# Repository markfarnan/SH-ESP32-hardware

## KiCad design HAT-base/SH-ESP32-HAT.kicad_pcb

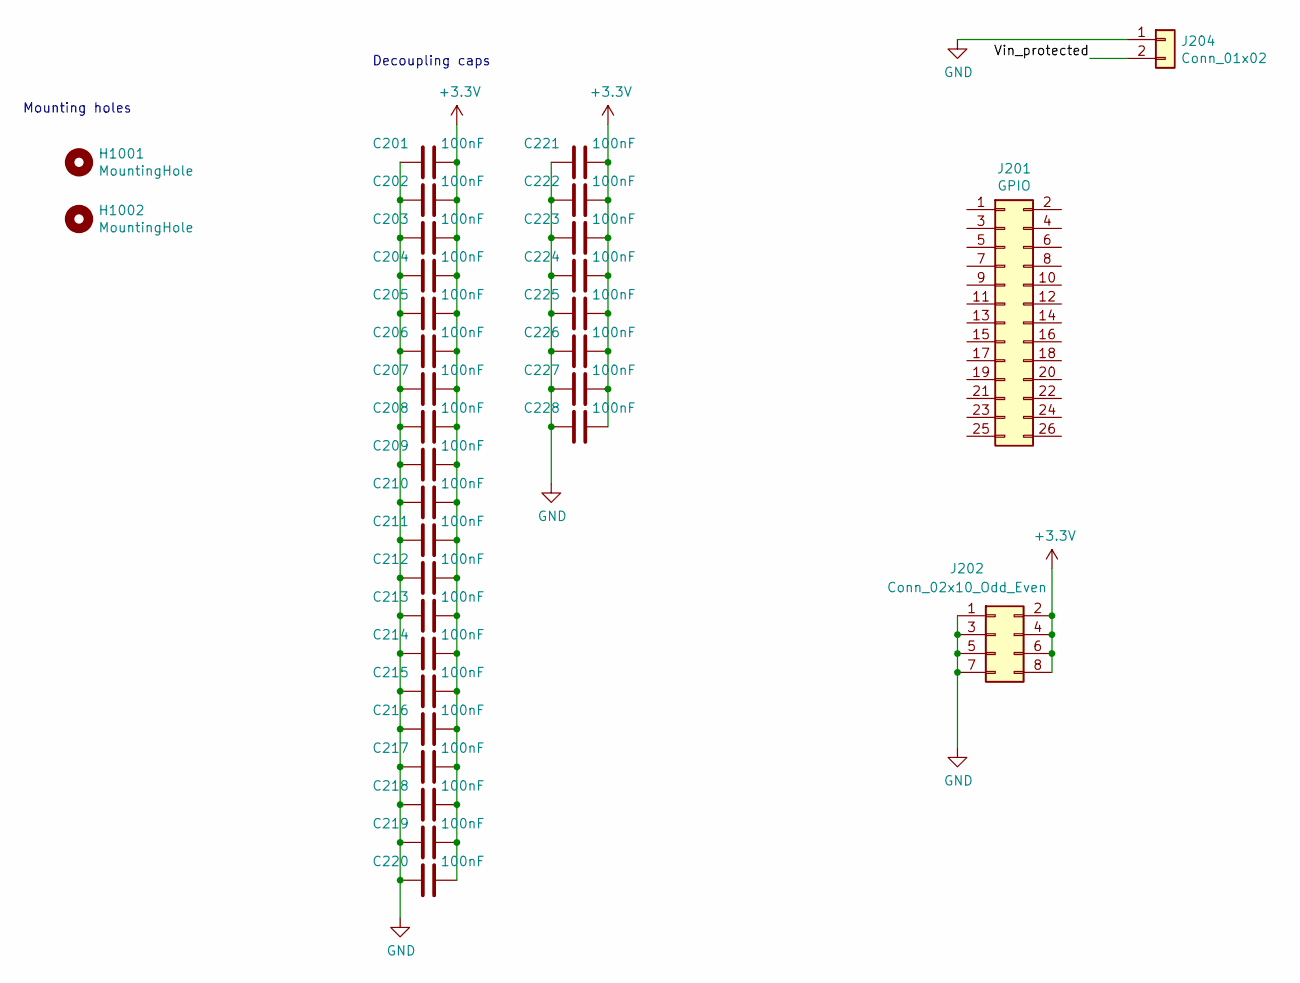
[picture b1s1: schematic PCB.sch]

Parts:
C201, C202, C203, C204, C205, C206, C207, C208, C209, C210, C211, C212, C213, C214, C215, C216, C217, C218, C219, C220, C221, C222, C223, C224, C225, C226, C227, C228: 100nF; C_0402_1005Metric; LCSC C1525
H1001, H1002: MountingHole; MountingHole_3.2mm_M3_Unplated
J201: GPIO; PinHeader_2x13_P2.54mm_Vertical; LCSC C358701
J202: Conn_02x10_Odd_Even; PinHeader_2x04_P2.54mm_Vertical; LCSC C358699
J204: Conn_01x02; PinHeader_1x02_P2.54mm_Vertical; LCSC C376075

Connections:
+3V3: C201.2, C202.2, C203.2, C204.2, C205.2, C206.2, C207.2, C208.2, C209.2, C210.2, C211.2, C212.2, C213.2, C214.2, C215.2, C216.2, C217.2, C218.2, C219.2, C220.2, C221.2, C222.2, C223.2, C224.2, C225.2, C226.2, C227.2, C228.2, J202.2, J202.4, J202.6, J202.8
/PCB/Vin_protected: J204.2
GND: C201.1, C202.1, C203.1, C204.1, C205.1, C206.1, C207.1, C208.1, C209.1, C210.1, C211.1, C212.1, C213.1, C214.1, C215.1, C216.1, C217.1, C218.1, C219.1, C220.1, C221.1, C222.1, C223.1, C224.1, C225.1, C226.1, C227.1, C228.1, J202.1, J202.3, J202.5, J202.7, J204.1

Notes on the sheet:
Mounting holes
Decoupling caps

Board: 4 copper layers, 33 parts (0 on the bottom side), 2 nets, no tracks yet.

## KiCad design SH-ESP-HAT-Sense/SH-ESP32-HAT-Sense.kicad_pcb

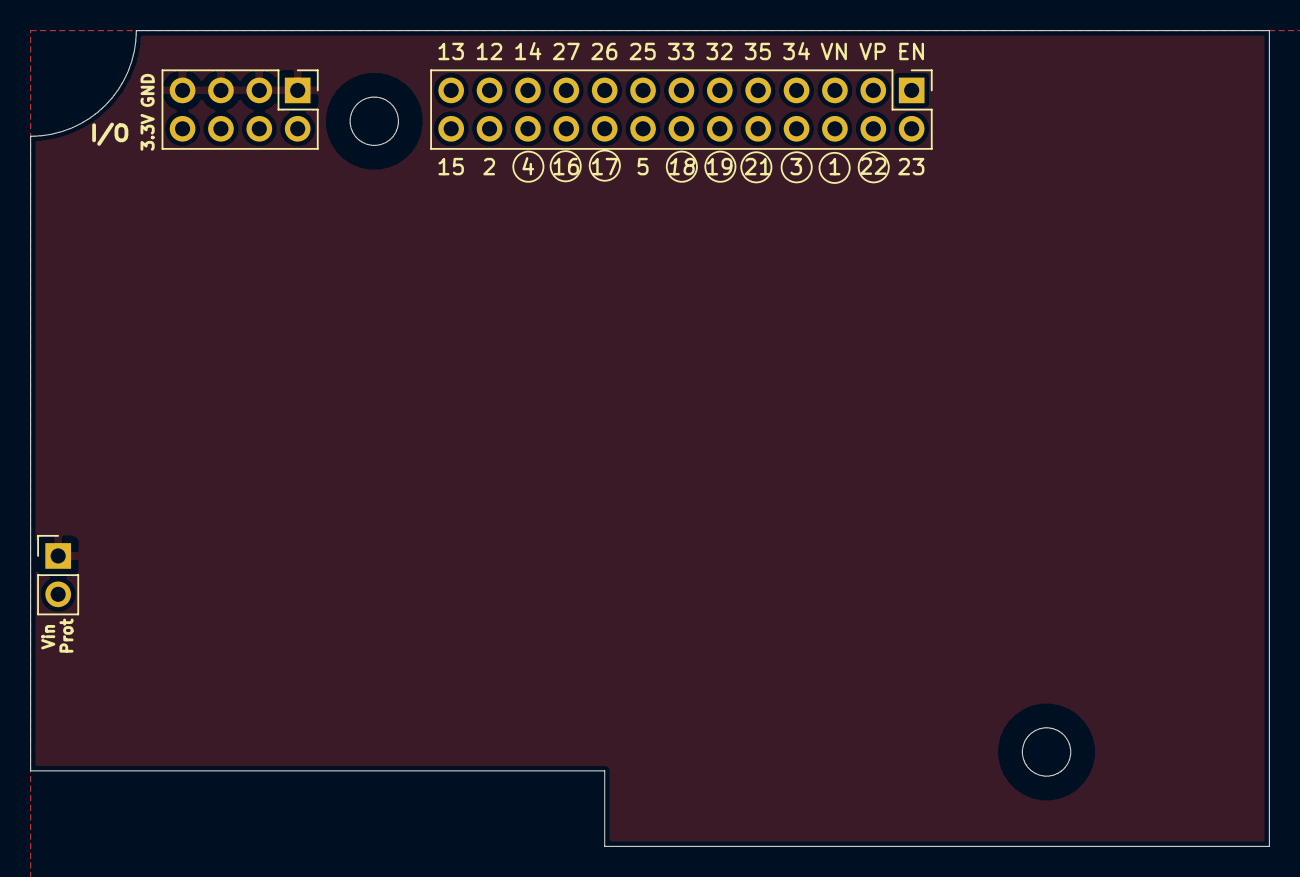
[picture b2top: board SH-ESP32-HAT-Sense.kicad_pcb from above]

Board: 4 copper layers, 82.0 x 54.0 mm, 5 parts (0 on the bottom side), 2 nets.

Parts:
H1001, H1002: MountingHole; MountingHole_3.2mm_M3_Unplated
J201: GPIO; PinHeader_2x13_P2.54mm_Vertical
J202: Conn_02x10_Odd_Even; PinHeader_2x04_P2.54mm_Vertical
J204: Conn_01x02; PinHeader_1x02_P2.54mm_Vertical

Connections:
+3V3: J202.2, J202.4, J202.6, J202.8
GND: J202.1, J202.3, J202.5, J202.7, J204.1

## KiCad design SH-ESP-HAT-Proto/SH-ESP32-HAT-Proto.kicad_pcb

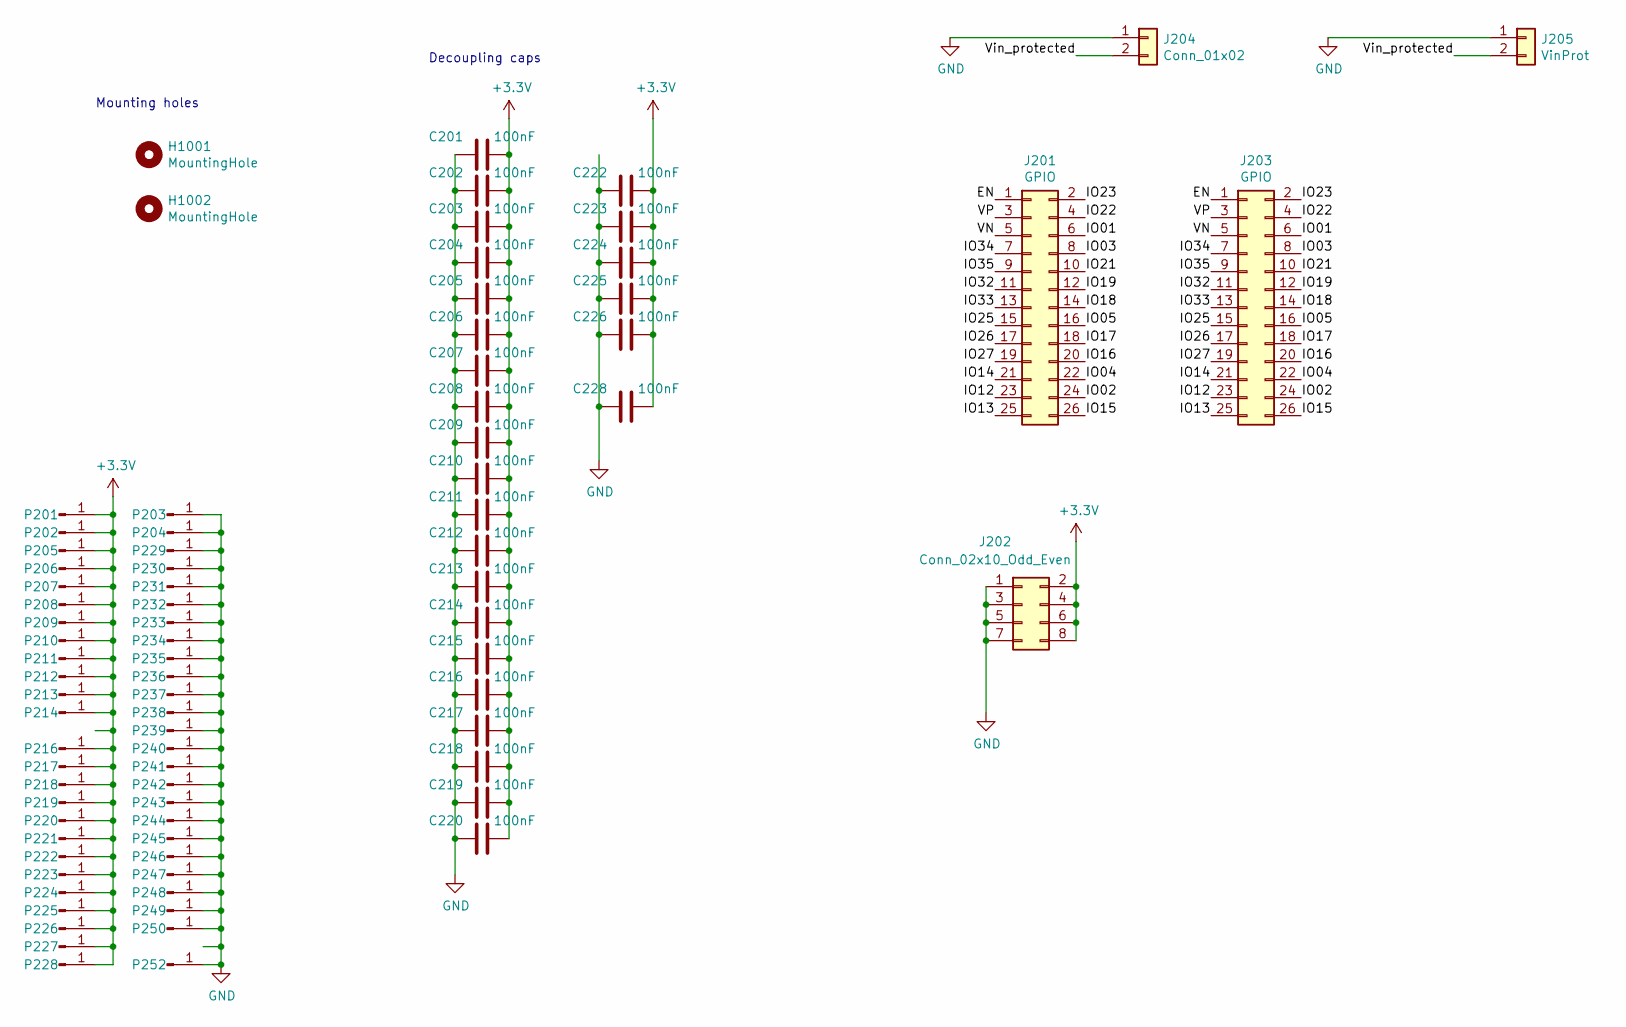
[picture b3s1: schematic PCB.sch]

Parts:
C201, C202, C203, C204, C205, C206, C207, C208, C209, C210, C211, C212, C213, C214, C215, C216, C217, C218, C219, C220, C222, C223, C224, C225, C226, C228: 100nF; C_0402_1005Metric; LCSC C1525
H1001, H1002: MountingHole; MountingHole_3.2mm_M3_Unplated
J201, J203: GPIO; PinHeader_2x13_P2.54mm_Vertical; LCSC C358701
J202: Conn_02x10_Odd_Even; PinHeader_2x04_P2.54mm_Vertical; LCSC C358699
J204: Conn_01x02; PinHeader_1x02_P2.54mm_Vertical; LCSC C376075
J205: VinProt; PinHeader_1x02_P2.54mm_Vertical; LCSC C376075
P201, P202, P203, P204, P205, P206, P207, P208, P209, P210, P211, P212, P213, P214, P216, P217, P218, P219, P220, P221, P222, P223, P224, P225, P226, P227, P228, P229, P230, P231, P232, P233, P234, P235, P236, P237, P238, P239, P240, P241, P242, P243, P244, P245, P246, P247, P248, P249, P250, P252: Conn_01x01_Male; ProtoPad-Drill1mm

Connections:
+3V3: C201.2, C202.2, C203.2, C204.2, C205.2, C206.2, C207.2, C208.2, C209.2, C210.2, C211.2, C212.2, C213.2, C214.2, C215.2, C216.2, C217.2, C218.2, C219.2, C220.2, C222.2, C223.2, C224.2, C225.2, C226.2, C228.2, J202.2, J202.4, J202.6, J202.8, P201.1, P202.1, P205.1, P206.1, P207.1, P208.1, P209.1, P210.1, P211.1, P212.1, P213.1, P214.1, P216.1, P217.1, P218.1, P219.1, P220.1, P221.1, P222.1, P223.1, P224.1, P225.1, P226.1, P227.1, P228.1
/PCB/EN: J201.1, J203.1
/PCB/IO01: J201.6, J203.6
/PCB/IO02: J201.24, J203.24
/PCB/IO03: J201.8, J203.8
/PCB/IO04: J201.22, J203.22
/PCB/IO05: J201.16, J203.16
/PCB/IO12: J201.23, J203.23
/PCB/IO13: J201.25, J203.25
/PCB/IO14: J201.21, J203.21
/PCB/IO15: J201.26, J203.26
/PCB/IO16: J201.20, J203.20
/PCB/IO17: J201.18, J203.18
/PCB/IO18: J201.14, J203.14
/PCB/IO19: J201.12, J203.12
/PCB/IO21: J201.10, J203.10
/PCB/IO22: J201.4, J203.4
/PCB/IO23: J201.2, J203.2
/PCB/IO25: J201.15, J203.15
/PCB/IO26: J201.17, J203.17
/PCB/IO27: J201.19, J203.19
/PCB/IO32: J201.11, J203.11
/PCB/IO33: J201.13, J203.13
/PCB/IO34: J201.7, J203.7
/PCB/IO35: J201.9, J203.9
/PCB/VN: J201.5, J203.5
/PCB/VP: J201.3, J203.3
/PCB/Vin_protected: J204.2, J205.2
GND: C201.1, C202.1, C203.1, C204.1, C205.1, C206.1, C207.1, C208.1, C209.1, C210.1, C211.1, C212.1, C213.1, C214.1, C215.1, C216.1, C217.1, C218.1, C219.1, C220.1, C222.1, C223.1, C224.1, C225.1, C226.1, C228.1, J202.1, J202.3, J202.5, J202.7, J204.1, J205.1, P203.1, P204.1, P229.1, P230.1, P231.1, P232.1, P233.1, P234.1, P235.1, P236.1, P237.1, P238.1, P239.1, P240.1, P241.1, P242.1, P243.1, P244.1, P245.1, P246.1, P247.1, P248.1, P249.1, P250.1, P252.1

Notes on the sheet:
Mounting holes
Decoupling caps

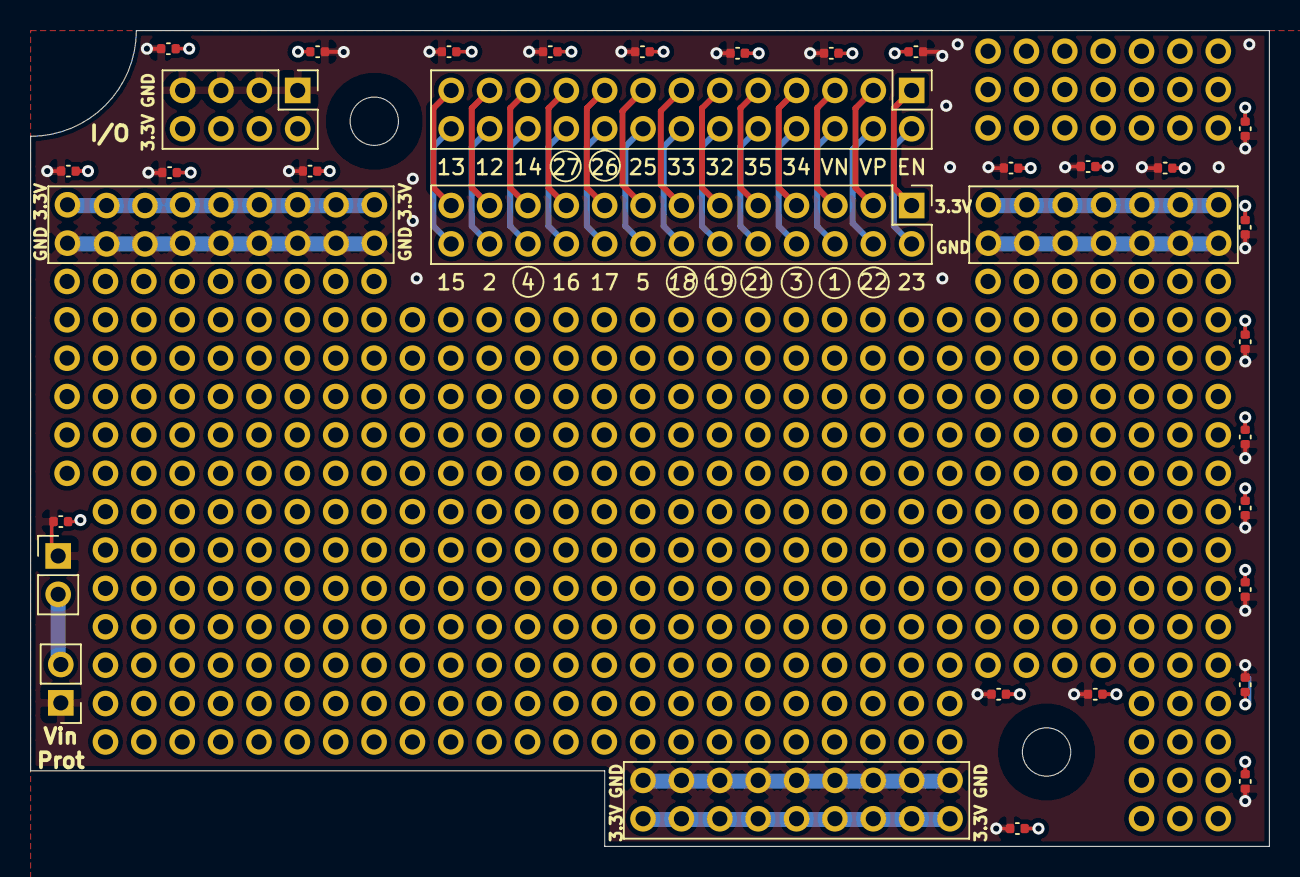
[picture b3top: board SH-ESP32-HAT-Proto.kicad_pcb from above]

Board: 4 copper layers, 82.0 x 54.0 mm, 83 parts (0 on the bottom side), 29 nets.

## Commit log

2020-11-14 Initial base, and board-of-holes proto
2020-11-15 Remove old files
2020-11-15 HAT-Proto with Holes. Cleaned, new round holes and copper fills working again
2020-11-15 Removed old Hat-Base - New one comming
2020-11-15 Rename project files to match directory. Hat-with-Holes ! (Prototyping)
2020-11-15 Blank Template Hat project. COPY before using
2020-11-15 Hat-Sense starting point

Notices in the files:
HAT-base/SH-ESP32-HAT.kicad_pcb:
Sailor Hat for ESP32 is licensed under CC BY-SA 4.0.
